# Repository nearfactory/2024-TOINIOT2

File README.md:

# TOINIOT2 2024 Main-Repo

TOINIOT² 2024年度 開発用メインリポジトリ

回路/基板データ・CADデータ・プログラムコード・プレゼンシートなどのデータ共有/保存用

[現時点での設計](https://a360.co/4b5pnYN)

[チーム内Wiki](https://github.com/nearfactory/2024-TOINIOT2/wiki)

## Follow us!

* X (Twitter) | [@toiniot2](https://x.com/toiniot2/)

* Instagram | [toiniot2](https://www.instagram.com/toiniot2/)

* YouTube | [@TOINIOT2](https://www.youtube.com/channel/UCjIjmQF-FIEdHT7s-4lD-6A)

* Team Blog | [TOINIOT² Blog](https://toiniot2-wakayama.github.io/Main/index.html)

## Presentation-Sheet

### 関西ブロック大会 2025.01.14 掲出

### リツモリカップ 2025.02.23 掲出

## Rules
* 📂 Discord上の _#GitHub_ チャンネルを活用してアップロード済みデータについての情報交換をしっかり!

* 🗣 コミュニケーションを頻繁にとる!!!!

* 👣 目標は高く、活動は地道に。

* 🧪 実験を実験を面倒くさがらない、小さな実験の積み重ねでロボットは完成する。

* 📚 率先して技術・知識の習得につとめる。

* 🤜 自らの担当に縛られすぎず、他の担当の手伝いもできるとベスト。

* 👥 自分が困っているときは遠慮なくメンバーにヘルプを求め、メンバーが困っているときは躊躇せずヘルプする!!!!

* 💪 **これが最後のRCJ。やり残しがないようにしよう。**

## Members
* NearFactory [@nearfactory](https://x.com/nearfactory/)

  機体設計・回路/基板設計・プログラム・プレゼンシート　担当

* maguronoosushi0807 [@_Rts87](https://x.com/_Rts87)

  回路/基板設計・プログラム　担当
  
* 010

  広報・ブログ・機体組立て　担当

* tobi

  電池監視員　担当

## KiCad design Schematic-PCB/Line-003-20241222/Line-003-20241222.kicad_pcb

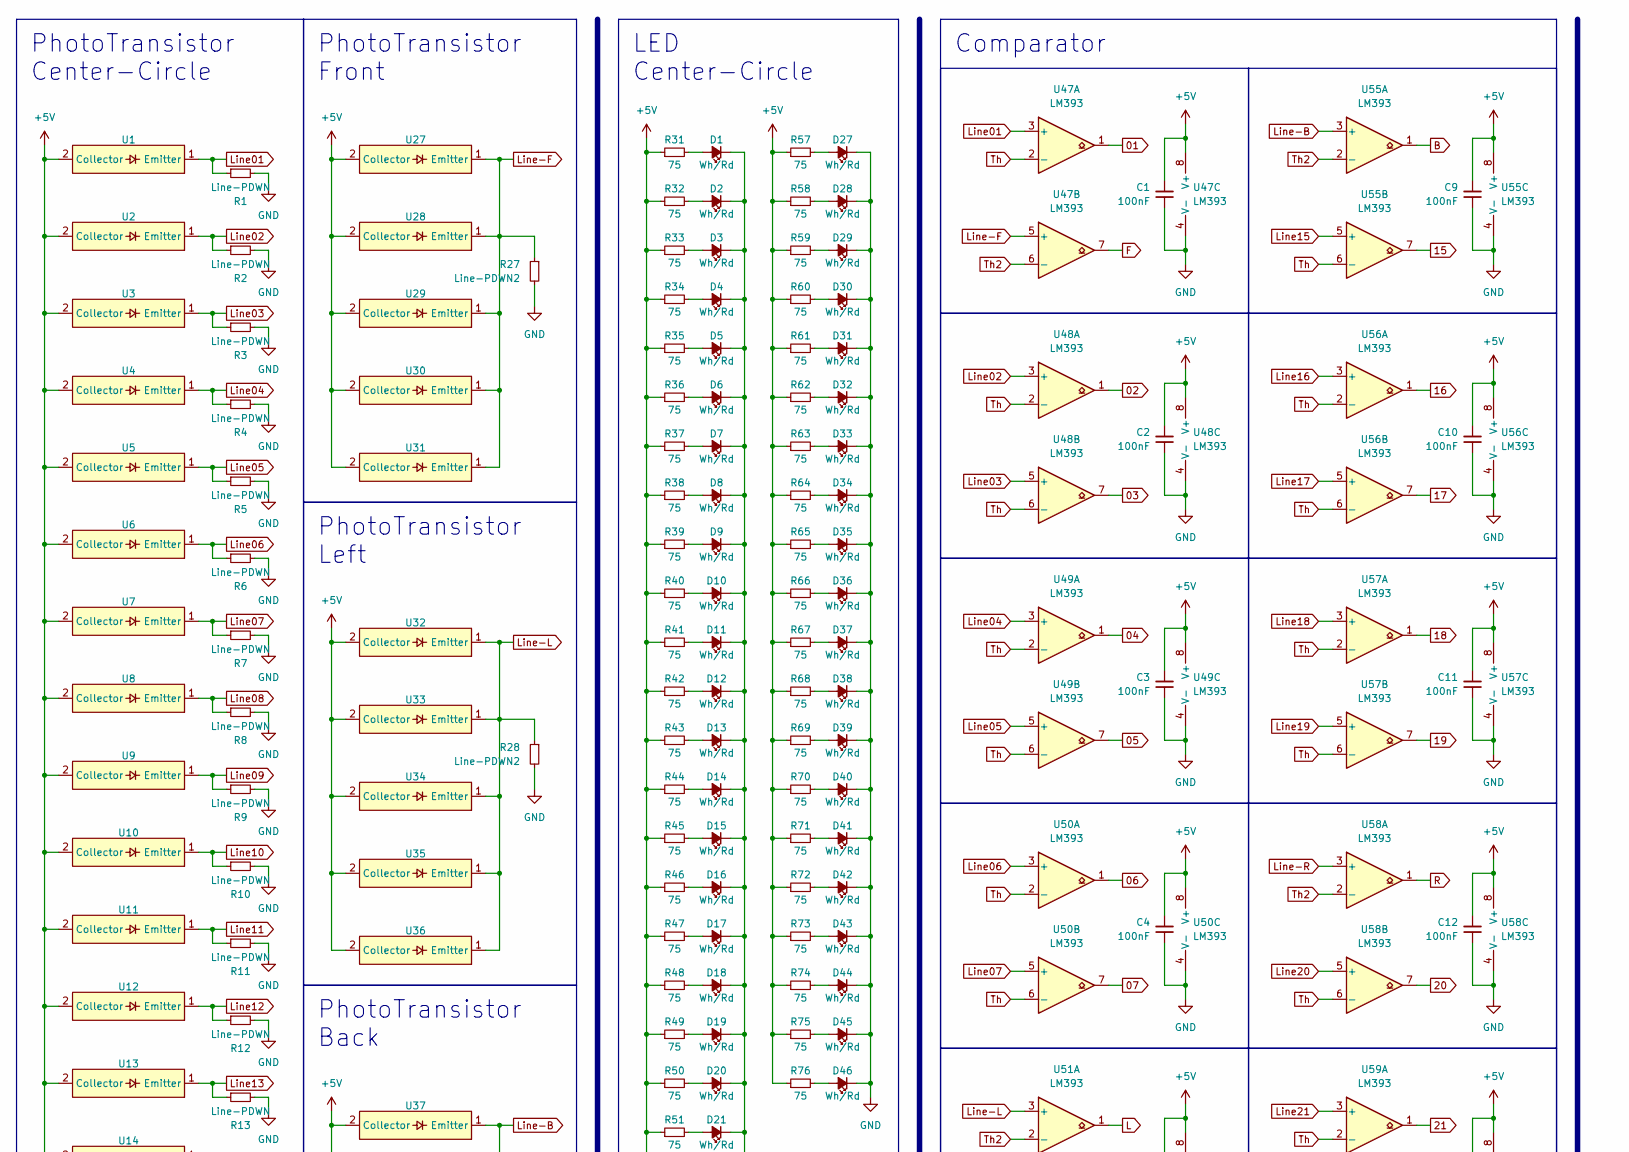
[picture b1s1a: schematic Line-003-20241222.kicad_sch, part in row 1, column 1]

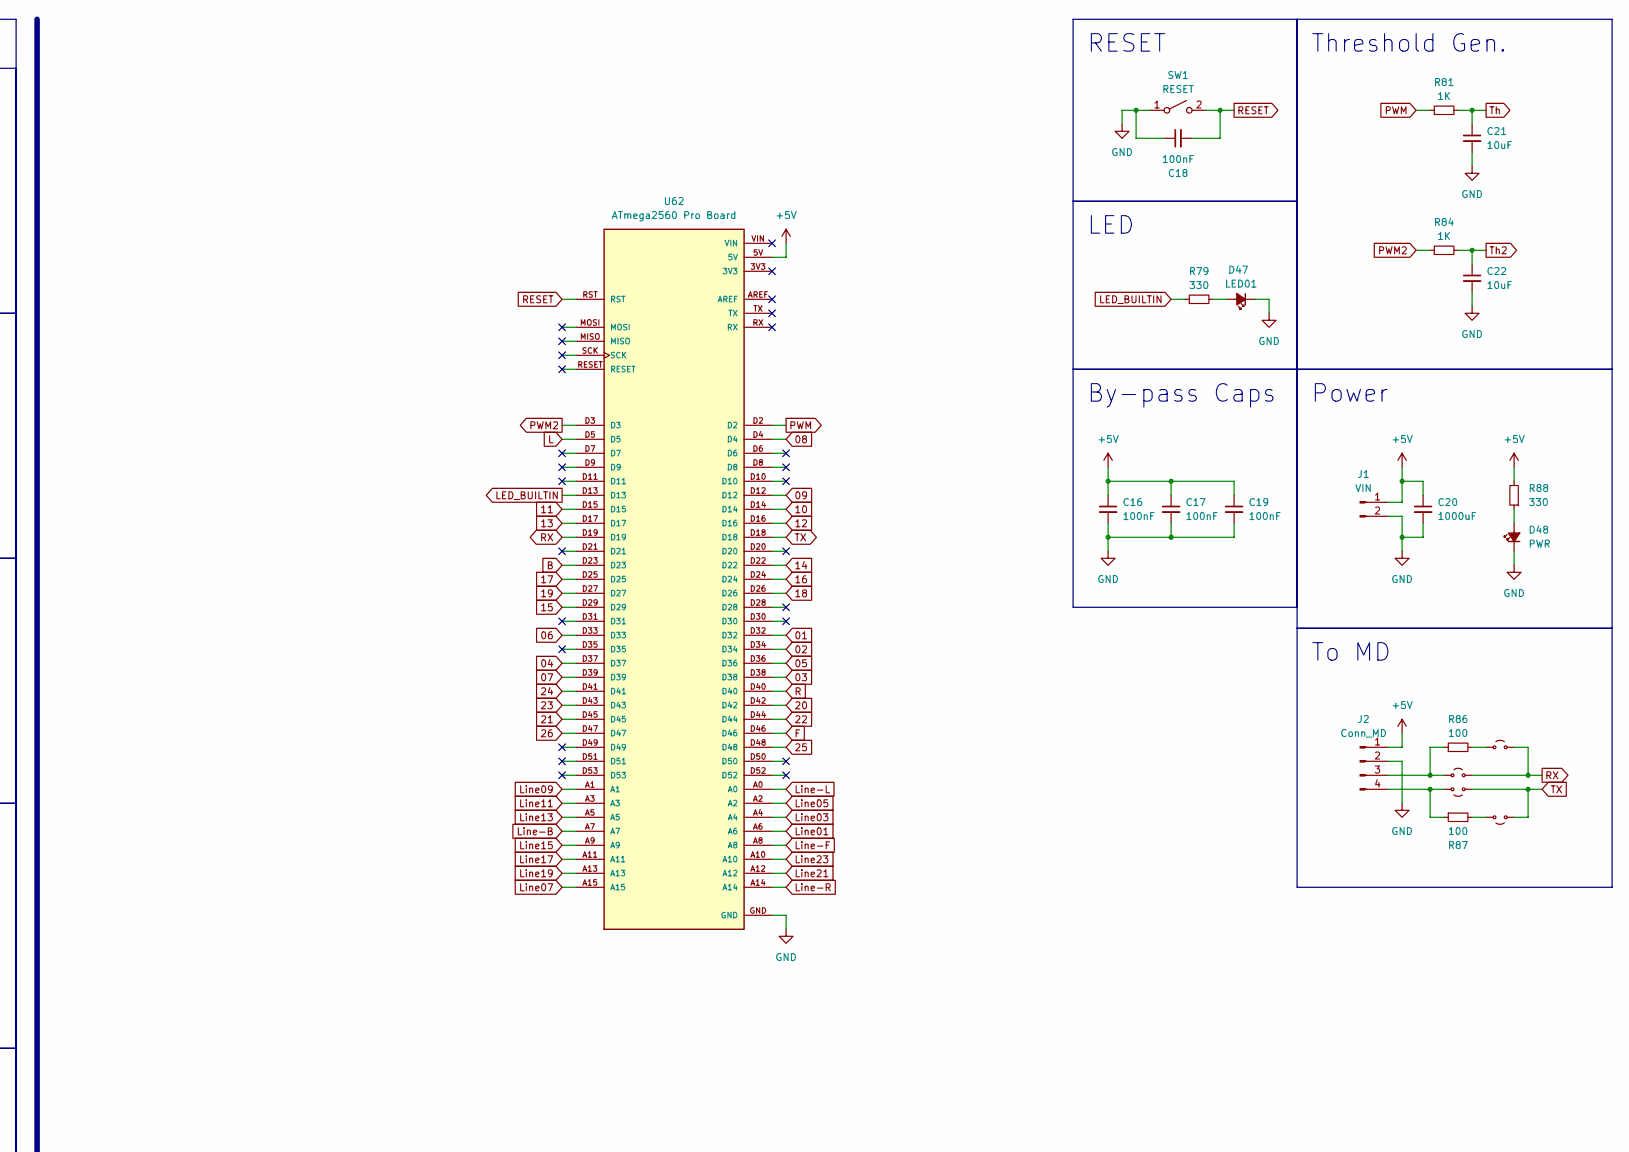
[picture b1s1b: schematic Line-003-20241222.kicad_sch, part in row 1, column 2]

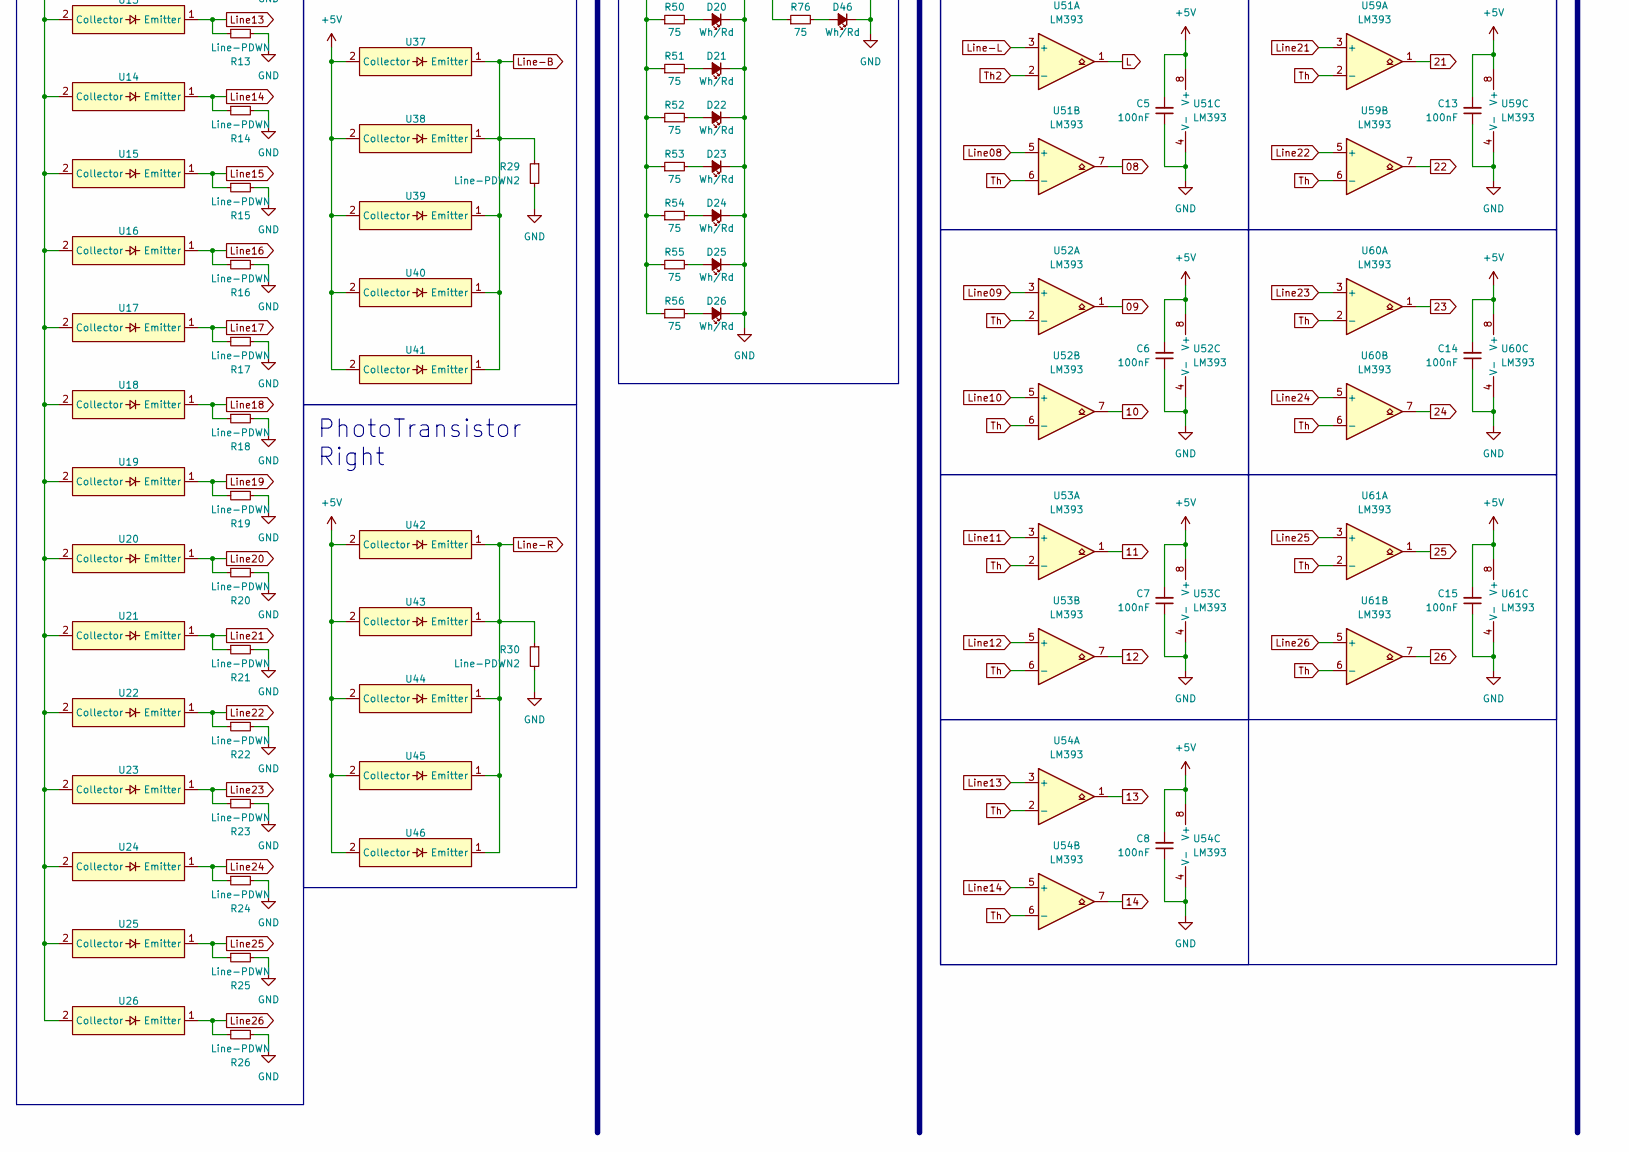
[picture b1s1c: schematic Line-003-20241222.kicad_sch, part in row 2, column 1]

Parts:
C1, C2, C3, C4, C5, C6, C7, C8, C9, C10, C11, C12, C13, C14, C15, C16, C17, C18, C19: 100nF; C_0603_1608Metric
C20: 1000uF; CP_Radial_D10.0mm_P5.00mm
C21, C22: 10uF; C_0805_2012Metric
D1, D2, D3, D4, D5, D6, D7, D8, D9, D10, D11, D12, D13, D14, D15, D16, D17, D18, D19, D20, D21, D22, D23, D24, D25, D26, D27, D28, D29, D30, D31, D32, D33, D34, D35, D36, D37, D38, D39, D40, D41, D42, D43, D44, D45, D46: Wh/Rd; LED-3mm
D47: LED01; LED_0603_1608Metric
D48: PWR; LED_0603_1608Metric
J1: VIN; JST_XH_S2B-XH-A-1_1x02_P2.50mm_Horizontal
J2: Conn_MD; Connector-MD
JP7, JP8, JP9, JP10: Jumper_2_Small_Open; SolderJumper-2_P1.3mm_Open_Pad1.0x1.5mm
R1, R2, R3, R4, R5, R6, R7, R8, R9, R10, R11, R12, R13, R14, R15, R16, R17, R18, R19, R20, R21, R22, R23, R24, R25, R26: Line-PDWN; R_0603_1608Metric
R27, R28, R29, R30: Line-PDWN2; R_0603_1608Metric
R31, R32, R33, R34, R35, R36, R37, R38, R39, R40, R41, R42, R43, R44, R45, R46, R47, R48, R49, R50, R51, R52, R53, R54, R55, R56, R57, R58, R59, R60, R61, R62, R63, R64, R65, R66, R67, R68, R69, R70, R71, R72, R73, R74, R75, R76: 75; R_0603_1608Metric
R79, R88: 330; R_0603_1608Metric
R81, R84: 1K; R_0603_1608Metric
R86, R87: 100; R_0603_1608Metric
SW1: RESET; Tactile1
U1, U2, U3, U4, U5, U6, U7, U8, U9, U10, U11, U12, U13, U14, U15, U16, U17, U18, U19, U20, U21, U22, U23, U24, U25, U26, U27, U28, U29, U30, U31, U32, U33, U34, U35, U36, U37, U38, U39, U40, U41, U42, U43, U44, U45, U46: NJL7502L
U47, U48, U49, U50, U51, U52, U53, U54, U55, U56, U57, U58, U59, U60, U61: LM393; SOP-8_3.9x4.9mm_P1.27mm
U62: ATmega2560 Pro Board; ATmega2560Pro Board; PARTREV 12/May/2017

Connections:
01: U47.1, U62.D32
02: U48.1, U62.D34
03: U48.7, U62.D38
04: U49.1, U62.D37
05: U49.7, U62.D36
06: U50.1, U62.D33
07: U50.7, U62.D39
08: U51.7, U62.D4
09: U52.1, U62.D12
10: U52.7, U62.D14
11: U53.1, U62.D15
12: U53.7, U62.D16
13: U54.1, U62.D17
14: U54.7, U62.D22
15: U55.7, U62.D29
16: U56.1, U62.D24
17: U56.7, U62.D25
18: U57.1, U62.D26
19: U57.7, U62.D27
20: U58.7, U62.D42
21: U59.1, U62.D45
22: U59.7, U62.D44
23: U60.1, U62.D43
24: U60.7, U62.D41
25: U61.1, U62.D48
26: U61.7, U62.D47
+5V: C1.2, C2.2, C3.2, C4.2, C5.2, C6.2, C7.2, C8.2, C9.2, C10.2, C11.2, C12.2, C13.2, C14.2, C15.2, C16.1, C17.1, C19.1, C20.1, J1.1, J2.1, R31.1, R32.1, R33.1, R34.1, R35.1, R36.1, R37.1, R38.1, R39.1, R40.1, R41.1, R42.1, R43.1, R44.1, R45.1, R46.1, R47.1, R48.1, R49.1, R50.1, R51.1, R52.1, R53.1, R54.1, R55.1, R56.1, R57.1, R58.1, R59.1, R60.1, R61.1, R62.1, R63.1, R64.1, R65.1, R66.1, R67.1, R68.1, R69.1, R70.1, R71.1, R72.1, R73.1, R74.1, R75.1, R76.1, R88.2, U1.2 (Collector), U2.2 (Collector), U3.2 (Collector), U4.2 (Collector), U5.2 (Collector), U6.2 (Collector), U7.2 (Collector), U8.2 (Collector), U9.2 (Collector), U10.2 (Collector), U11.2 (Collector), U12.2 (Collector), U13.2 (Collector), U14.2 (Collector), U15.2 (Collector), U16.2 (Collector), U17.2 (Collector), U18.2 (Collector), U19.2 (Collector), U20.2 (Collector), U21.2 (Collector), U22.2 (Collector), U23.2 (Collector), U24.2 (Collector), U25.2 (Collector), U26.2 (Collector), U27.2 (Collector), U28.2 (Collector), U29.2 (Collector), U30.2 (Collector), U31.2 (Collector), U32.2 (Collector), U33.2 (Collector), U34.2 (Collector), U35.2 (Collector), U36.2 (Collector), U37.2 (Collector), U38.2 (Collector), U39.2 (Collector), U40.2 (Collector), U41.2 (Collector), U42.2 (Collector), U43.2 (Collector), U44.2 (Collector), U45.2 (Collector), U46.2 (Collector), U47.8 (V+), U48.8 (V+), U49.8 (V+), U50.8 (V+), U51.8 (V+), U52.8 (V+), U53.8 (V+), U54.8 (V+), U55.8 (V+), U56.8 (V+), U57.8 (V+), U58.8 (V+), U59.8 (V+), U60.8 (V+), U61.8 (V+), U62.5V
B: U55.1, U62.D23
F: U47.7, U62.D46
GND: C1.1, C2.1, C3.1, C4.1, C5.1, C6.1, C7.1, C8.1, C9.1, C10.1, C11.1, C12.1, C13.1, C14.1, C15.1, C16.2, C17.2, C18.1, C19.2, C20.2, C21.2, C22.2, D1.1 (K), D2.1 (K), D3.1 (K), D4.1 (K), D5.1 (K), D6.1 (K), D7.1 (K), D8.1 (K), D9.1 (K), D10.1 (K), D11.1 (K), D12.1 (K), D13.1 (K), D14.1 (K), D15.1 (K), D16.1 (K), D17.1 (K), D18.1 (K), D19.1 (K), D20.1 (K), D21.1 (K), D22.1 (K), D23.1 (K), D24.1 (K), D25.1 (K), D26.1 (K), D27.1 (K), D28.1 (K), D29.1 (K), D30.1 (K), D31.1 (K), D32.1 (K), D33.1 (K), D34.1 (K), D35.1 (K), D36.1 (K), D37.1 (K), D38.1 (K), D39.1 (K), D40.1 (K), D41.1 (K), D42.1 (K), D43.1 (K), D44.1 (K), D45.1 (K), D46.1 (K), D47.1 (K), D48.1 (K), J1.2, J2.2, R1.2, R2.2, R3.2, R4.2, R5.2, R6.2, R7.2, R8.2, R9.2, R10.2, R11.2, R12.2, R13.2, R14.2, R15.2, R16.2, R17.2, R18.2, R19.2, R20.2, R21.2, R22.2, R23.2, R24.2, R25.2, R26.2, R27.2, R28.2, R29.2, R30.2, SW1.1 (A), U47.4 (V-), U48.4 (V-), U49.4 (V-), U50.4 (V-), U51.4 (V-), U52.4 (V-), U53.4 (V-), U54.4 (V-), U55.4 (V-), U56.4 (V-), U57.4 (V-), U58.4 (V-), U59.4 (V-), U60.4 (V-), U61.4 (V-), U62.GND
L: U51.1, U62.D5
LED_BUILTIN: R79.1, U62.D13
Line01: R1.1, U1.1 (Emitter), U47.3 (+), U62.A6
Line02: R2.1, U2.1 (Emitter), U48.3 (+)
Line03: R3.1, U3.1 (Emitter), U48.5 (+), U62.A4
Line04: R4.1, U4.1 (Emitter), U49.3 (+)
Line05: R5.1, U5.1 (Emitter), U49.5 (+), U62.A2
Line06: R6.1, U6.1 (Emitter), U50.3 (+)
Line07: R7.1, U7.1 (Emitter), U50.5 (+), U62.A15
Line08: R8.1, U8.1 (Emitter), U51.5 (+)
Line09: R9.1, U9.1 (Emitter), U52.3 (+), U62.A1
Line10: R10.1, U10.1 (Emitter), U52.5 (+)
Line11: R11.1, U11.1 (Emitter), U53.3 (+), U62.A3
Line12: R12.1, U12.1 (Emitter), U53.5 (+)
Line13: R13.1, U13.1 (Emitter), U54.3 (+), U62.A5
Line14: R14.1, U14.1 (Emitter), U54.5 (+)
Line15: R15.1, U15.1 (Emitter), U55.5 (+), U62.A9
Line16: R16.1, U16.1 (Emitter), U56.3 (+)
Line17: R17.1, U17.1 (Emitter), U56.5 (+), U62.A11
Line18: R18.1, U18.1 (Emitter), U57.3 (+)
Line19: R19.1, U19.1 (Emitter), U57.5 (+), U62.A13
Line20: R20.1, U20.1 (Emitter), U58.5 (+)
Line21: R21.1, U21.1 (Emitter), U59.3 (+), U62.A12
Line22: R22.1, U22.1 (Emitter), U59.5 (+)
Line23: R23.1, U23.1 (Emitter), U60.3 (+), U62.A10
Line24: R24.1, U24.1 (Emitter), U60.5 (+)
Line25: R25.1, U25.1 (Emitter), U61.3 (+)
Line26: R26.1, U26.1 (Emitter), U61.5 (+)
Line-B: R29.1, U37.1 (Emitter), U38.1 (Emitter), U39.1 (Emitter), U40.1 (Emitter), U41.1 (Emitter), U55.3 (+), U62.A7
Line-F: R27.1, U27.1 (Emitter), U28.1 (Emitter), U29.1 (Emitter), U30.1 (Emitter), U31.1 (Emitter), U47.5 (+), U62.A8
Line-L: R28.1, U32.1 (Emitter), U33.1 (Emitter), U34.1 (Emitter), U35.1 (Emitter), U36.1 (Emitter), U51.3 (+), U62.A0
Line-R: R30.1, U42.1 (Emitter), U43.1 (Emitter), U44.1 (Emitter), U45.1 (Emitter), U46.1 (Emitter), U58.3 (+), U62.A14
unnamed: D1.2 (A), R31.2
unnamed: D2.2 (A), R32.2
unnamed: D3.2 (A), R33.2
unnamed: D4.2 (A), R34.2
unnamed: D5.2 (A), R35.2
unnamed: D6.2 (A), R36.2
unnamed: D7.2 (A), R37.2
unnamed: D8.2 (A), R38.2
unnamed: D9.2 (A), R39.2
unnamed: D10.2 (A), R40.2
unnamed: D11.2 (A), R41.2
unnamed: D12.2 (A), R42.2
unnamed: D13.2 (A), R43.2
unnamed: D14.2 (A), R44.2
unnamed: D15.2 (A), R45.2
unnamed: D16.2 (A), R46.2
unnamed: D17.2 (A), R47.2
unnamed: D18.2 (A), R48.2
unnamed: D19.2 (A), R49.2
unnamed: D20.2 (A), R50.2
unnamed: D21.2 (A), R51.2
unnamed: D22.2 (A), R52.2
unnamed: D23.2 (A), R53.2
unnamed: D24.2 (A), R54.2
unnamed: D25.2 (A), R55.2
unnamed: D26.2 (A), R56.2
unnamed: D27.2 (A), R57.2
unnamed: D28.2 (A), R58.2
unnamed: D29.2 (A), R59.2
unnamed: D30.2 (A), R60.2
unnamed: D31.2 (A), R61.2
unnamed: D32.2 (A), R62.2
unnamed: D33.2 (A), R63.2
unnamed: D34.2 (A), R64.2
unnamed: D35.2 (A), R65.2
unnamed: D36.2 (A), R66.2
unnamed: D37.2 (A), R67.2
unnamed: D38.2 (A), R68.2
unnamed: D39.2 (A), R69.2
unnamed: D40.2 (A), R70.2
unnamed: D41.2 (A), R71.2
unnamed: D42.2 (A), R72.2
unnamed: D43.2 (A), R73.2
unnamed: D44.2 (A), R74.2
unnamed: D45.2 (A), R75.2
unnamed: D46.2 (A), R76.2
unnamed: D47.2 (A), R79.2
unnamed: D48.2 (A), R88.1
unnamed: J2.3, JP7.1 (A), R86.1
unnamed: J2.4, JP8.1 (A), R87.1
unnamed: JP9.1 (A), R86.2
unnamed: JP10.1 (A), R87.2
PWM: R81.1, U62.D2
PWM2: R84.1, U62.D3
R: U58.1, U62.D40
RESET: C18.2, SW1.2 (B), U62.RST
RX: JP7.2 (B), JP9.2 (B), U62.D19
TX: JP8.2 (B), JP10.2 (B), U62.D18
Th: C21.1, R81.2, U47.2 (-), U48.2 (-), U48.6 (-), U49.2 (-), U49.6 (-), U50.2 (-), U50.6 (-), U51.6 (-), U52.2 (-), U52.6 (-), U53.2 (-), U53.6 (-), U54.2 (-), U54.6 (-), U55.6 (-), U56.2 (-), U56.6 (-), U57.2 (-), U57.6 (-), U58.6 (-), U59.2 (-), U59.6 (-), U60.2 (-), U60.6 (-), U61.2 (-), U61.6 (-)
Th2: C22.1, R84.2, U47.6 (-), U51.2 (-), U55.2 (-), U58.2 (-)

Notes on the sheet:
By-pass Caps
PhotoTransistor Back
LED Center-Circle
PhotoTransistor Front
PhotoTransistor Center-Circle
Threshold Gen.
RESET
LED
Comparator
Power
PhotoTransistor Right
PhotoTransistor Left
To MD

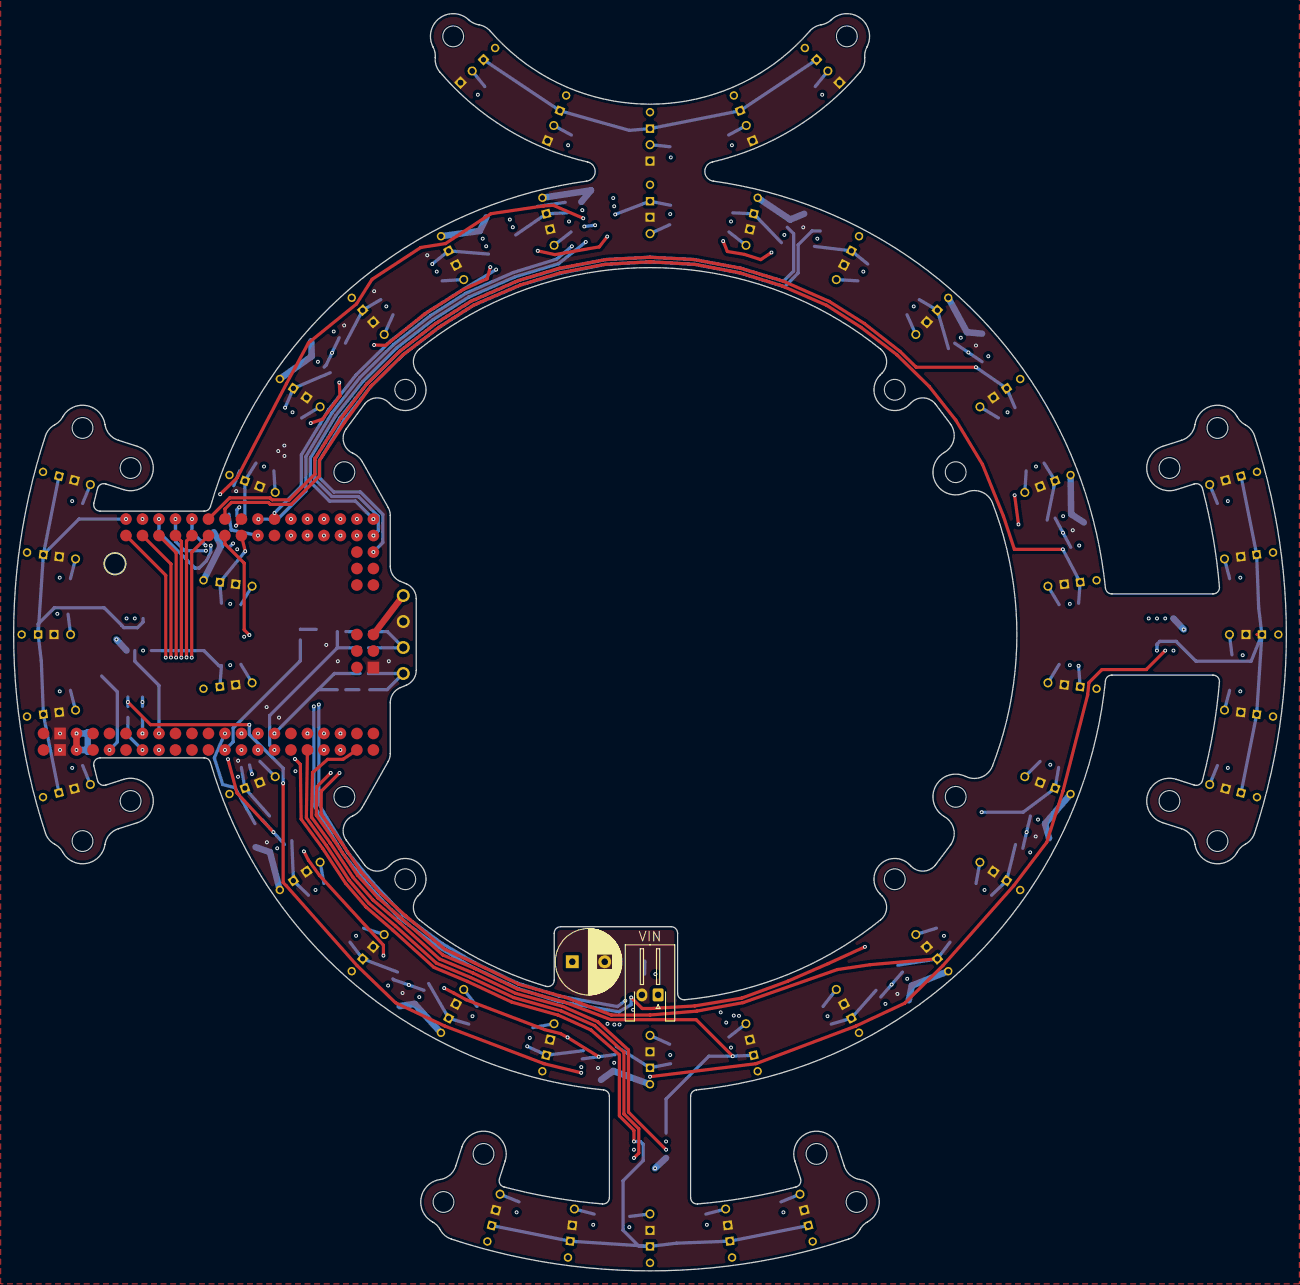
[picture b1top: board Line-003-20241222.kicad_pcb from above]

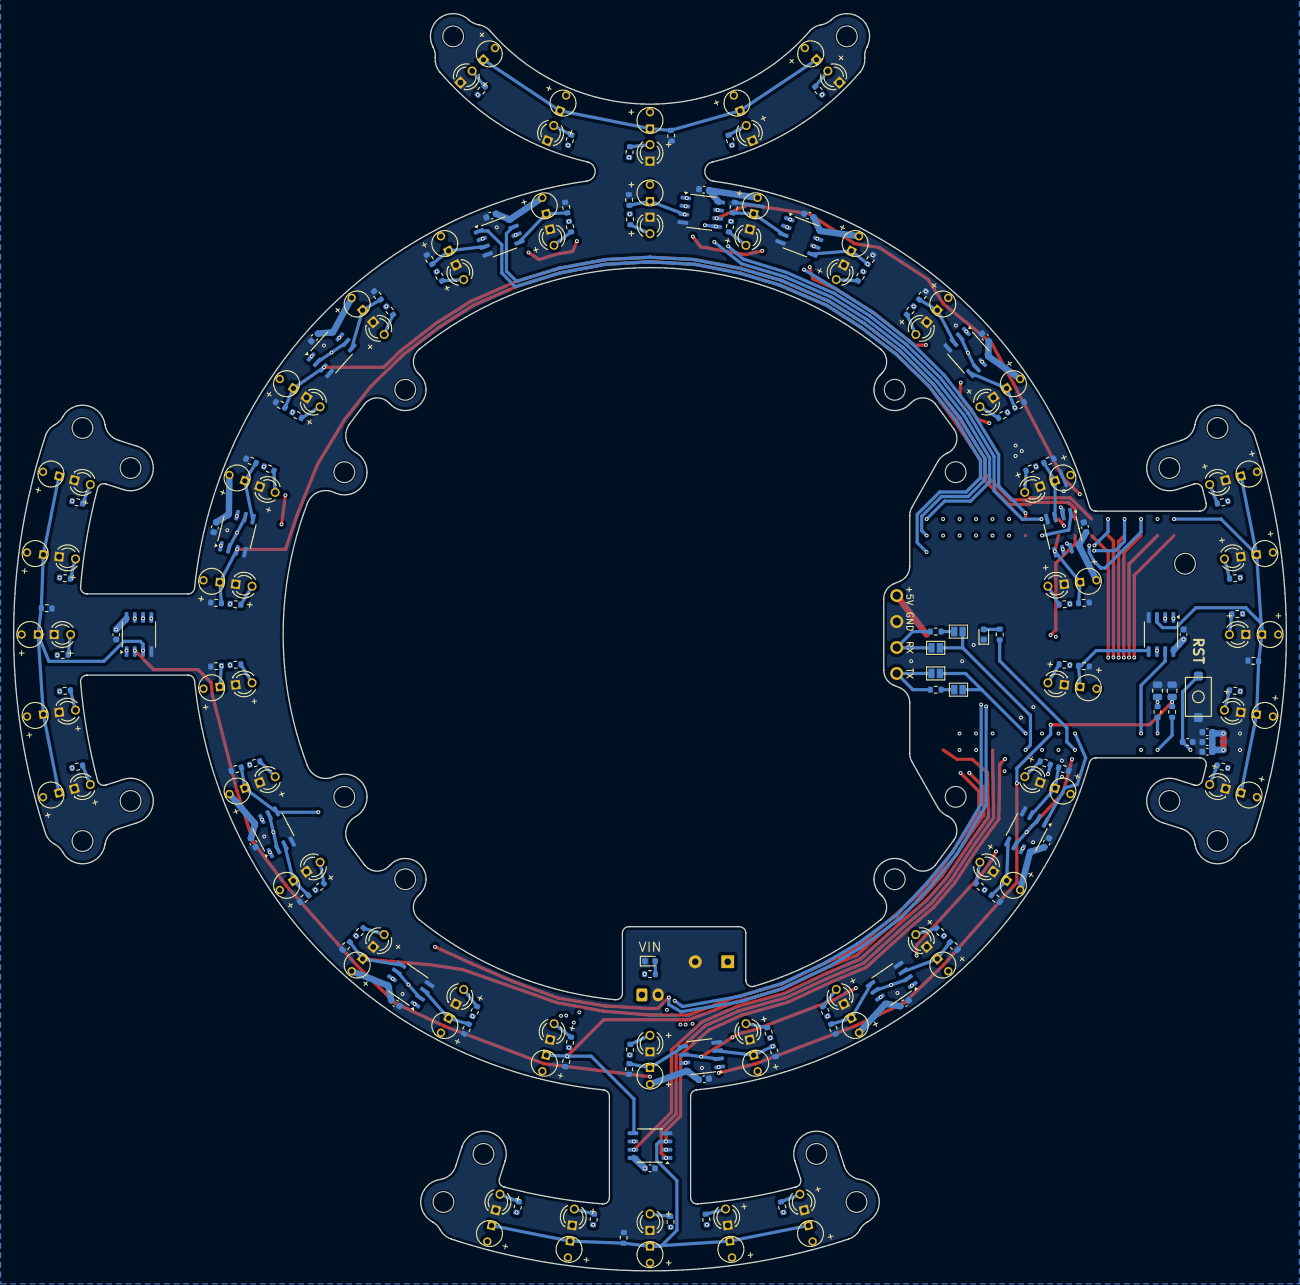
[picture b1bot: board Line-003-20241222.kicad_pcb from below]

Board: 4 copper layers, 196.0 x 193.6 mm, 221 parts (217 on the bottom side), 122 nets.

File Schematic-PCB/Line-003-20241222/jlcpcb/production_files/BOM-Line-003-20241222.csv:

Comment,Designator,Footprint,LCSC,Quantity
100nF,"C1,C10,C11,C12,C13,C14,C15,C16,C17,C18,C19,C2,C3,C4,C5,C6,C7,C8,C9",C_0603_1608Metric,C14663,19
10uF,"C21,C22",C_0805_2012Metric,C15850,2
1K,"R81,R84",R_0603_1608Metric,C21190,2
100,"R86,R87",R_0603_1608Metric,C22775,2
330,"R79,R88",R_0603_1608Metric,C23138,2
Line-PDWN2,"R27,R28,R29,R30",R_0603_1608Metric,C25804,4
RESET,SW1,Tactile1,C2844407,1
Line-PDWN,"R1,R10,R11,R12,R13,R14,R15,R16,R17,R18,R19,R2,R20,R21,R22,R23,R24,R25,R26,R3,R4,R5,R6,R7,R8,R9",R_0603_1608Metric,C4184,26
75,"R31,R32,R33,R34,R35,R36,R37,R38,R39,R40,R41,R42,R43,R44,R45,R46,R47,R48,R49,R50,R51,R52,R53,R54,R55,R56,R57,R58,R59,R60,R61,R62,R63,R64,R65,R66,R67,R68,R69,R70,R71,R72,R73,R74,R75,R76",R_0603_1608Metric,C4275,46
LM393,"U47,U48,U49,U50,U51,U52,U53,U54,U55,U56,U57,U58,U59,U60,U61",SOP-8_3.9x4.9mm_P1.27mm,C7955,15

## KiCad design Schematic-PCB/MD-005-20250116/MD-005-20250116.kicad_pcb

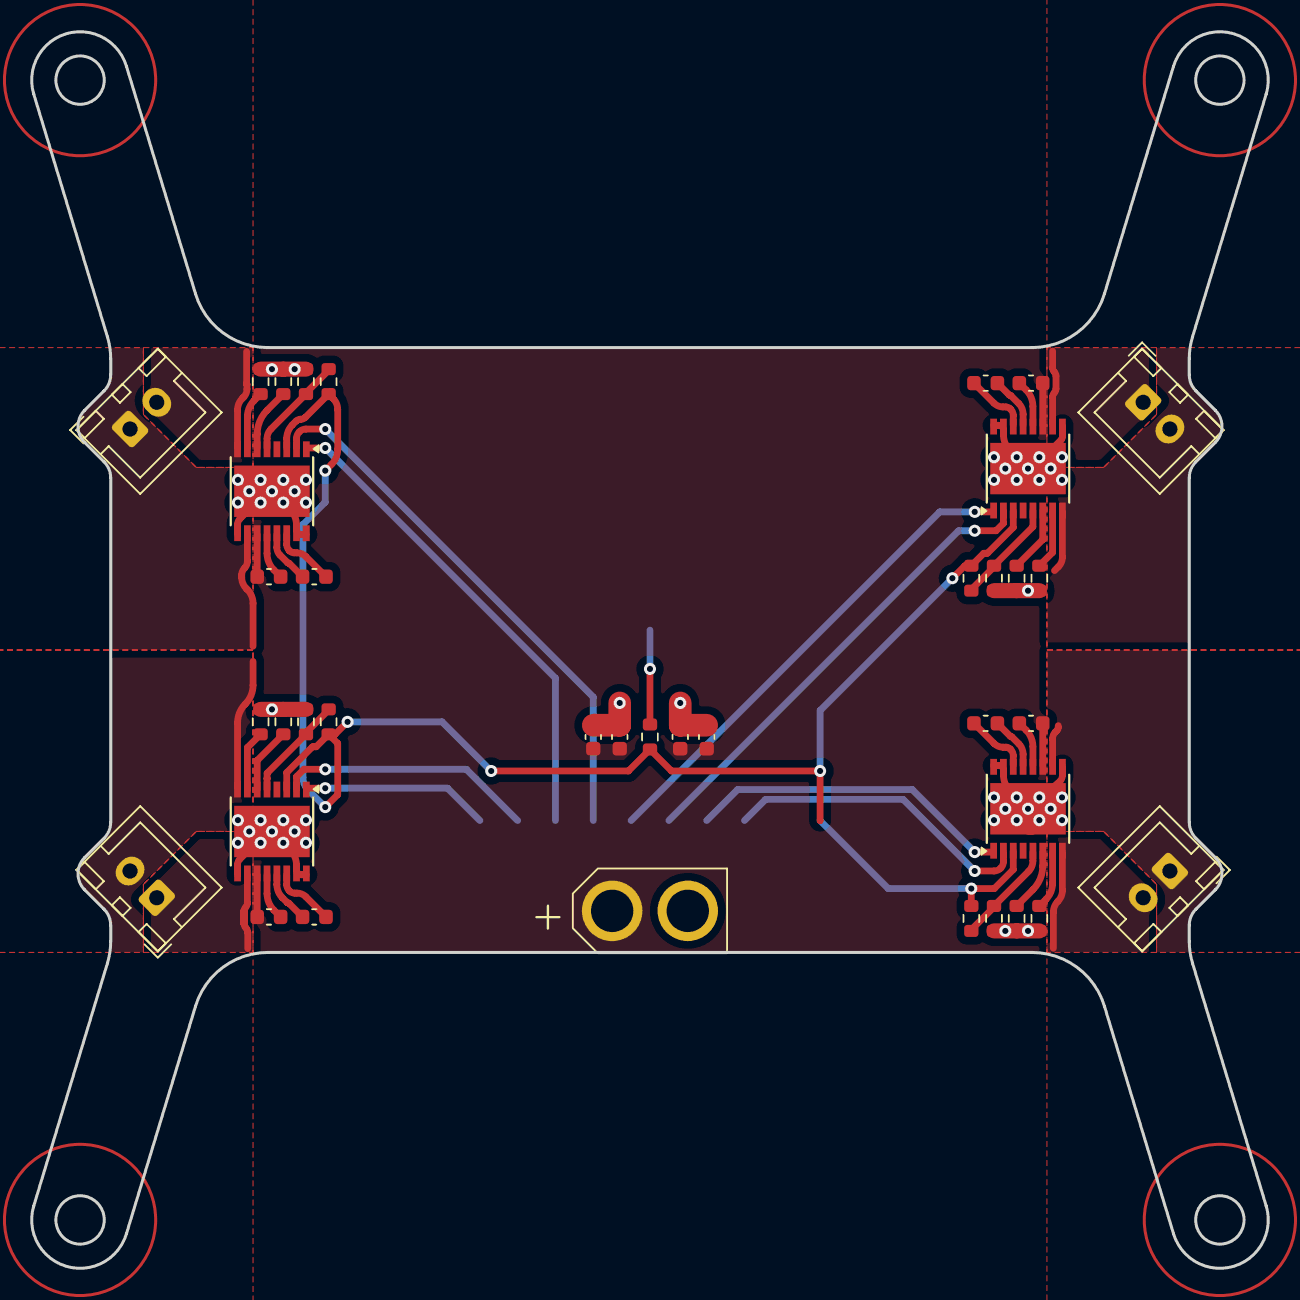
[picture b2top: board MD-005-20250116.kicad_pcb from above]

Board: 2 copper layers, 81.8 x 81.8 mm, 39 parts (1 on the bottom side), 36 nets.

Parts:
C1, C2: 4.7u; C_0603_1608Metric
C3, C4: 0.1u; C_0603_1608Metric
C5, C6, C9, C10: 22n; C_0603_1608Metric
C7, C8, C11, C12: 220n; C_0603_1608Metric
D1: PWR; LED_0805_2012Metric
J1: Conn_PWR; XT30U-M
J3, J4, J5, J6: Conn_01x02_Pin; JST_XH_B2B-XH-A_1x02_P2.50mm_Vertical
R1, R2, R10, R11: 2.49k; R_0603_1608Metric
R3: 330; R_0603_1608Metric
R4, R6, R12, R14: 10k; R_0603_1608Metric
R5, R7, R13, R15: NP; R_0603_1608Metric
R8, R9, R16, R17: 20k; R_0603_1608Metric
U1, U2, U3, U4: HTSSOP-16-1EP_4.4x5mm_P0.65mm_EP3.4x5mm

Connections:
GND: C1.2, C2.2, C3.2, C4.2, D1.1 (K), J1.2, R1.2, R2.2, R5.2, R7.2, R8.2, R9.2, R10.2, R11.2, R13.2, R15.2, R16.2, R17.2, U1.9 (PGND), U1.15 (GND), U1.16 (PMODE), U1.17 (GND), U2.9 (PGND), U2.15 (GND), U2.16 (PMODE), U2.17 (GND), U3.9 (PGND), U3.15 (GND), U3.16 (PMODE), U3.17 (GND), U4.9 (PGND), U4.15 (GND), U4.16 (PMODE), U4.17 (GND)
IMODE-1: R8.1, U1.7 (IMODE)
IMODE-2: R16.1, U2.7 (IMODE)
IMODE-3: R9.1, U3.7 (IMODE)
IMODE-4: R17.1, U4.7 (IMODE)
unnamed: D1.2 (A), R3.2
unnamed: C5.2, U1.13 (CPH)
unnamed: C5.1, U1.14 (CPL)
unnamed: R1.1, U1.6 (IPROPI)
unnamed: C7.1, U1.12 (VCP)
unnamed: C6.2, U2.13 (CPH)
unnamed: C6.1, U2.14 (CPL)
unnamed: R2.1, U2.6 (IPROPI)
unnamed: C8.1, U2.12 (VCP)
unnamed: C9.2, U3.13 (CPH)
unnamed: C9.1, U3.14 (CPL)
unnamed: R10.1, U3.6 (IPROPI)
unnamed: C11.1, U3.12 (VCP)
unnamed: C10.2, U4.13 (CPH)
unnamed: C10.1, U4.14 (CPL)
unnamed: R11.1, U4.6 (IPROPI)
unnamed: C12.1, U4.12 (VCP)
OUT1-1: J3.2, U1.8 (OUT1)
OUT1-2: J4.2, U2.8 (OUT1)
OUT1-3: J5.2, U3.8 (OUT1)
OUT1-4: J6.2, U4.8 (OUT1)
OUT2-1: J3.1, U1.10 (OUT2)
OUT2-2: J4.1, U2.10 (OUT2)
OUT2-3: J5.1, U3.10 (OUT2)
OUT2-4: J6.1, U4.10 (OUT2)
SLEEP-1: R3.1, R4.1, R6.1, R12.1, R14.1, U1.3 (SLEEP), U2.3 (SLEEP), U3.3 (SLEEP), U4.3 (SLEEP)
VCC: C1.1, C2.1, C3.1, C4.1, C7.2, C8.2, C11.2, C12.2, J1.1, U1.11 (VM), U2.11 (VM), U3.11 (VM), U4.11 (VM)
VREF-1: R4.2, R5.1, U1.5 (VREF)
VREF-2: R12.2, R13.1, U2.5 (VREF)
VREF-3: R6.2, R7.1, U3.5 (VREF)
VREF-4: R14.2, R15.1, U4.5 (VREF)

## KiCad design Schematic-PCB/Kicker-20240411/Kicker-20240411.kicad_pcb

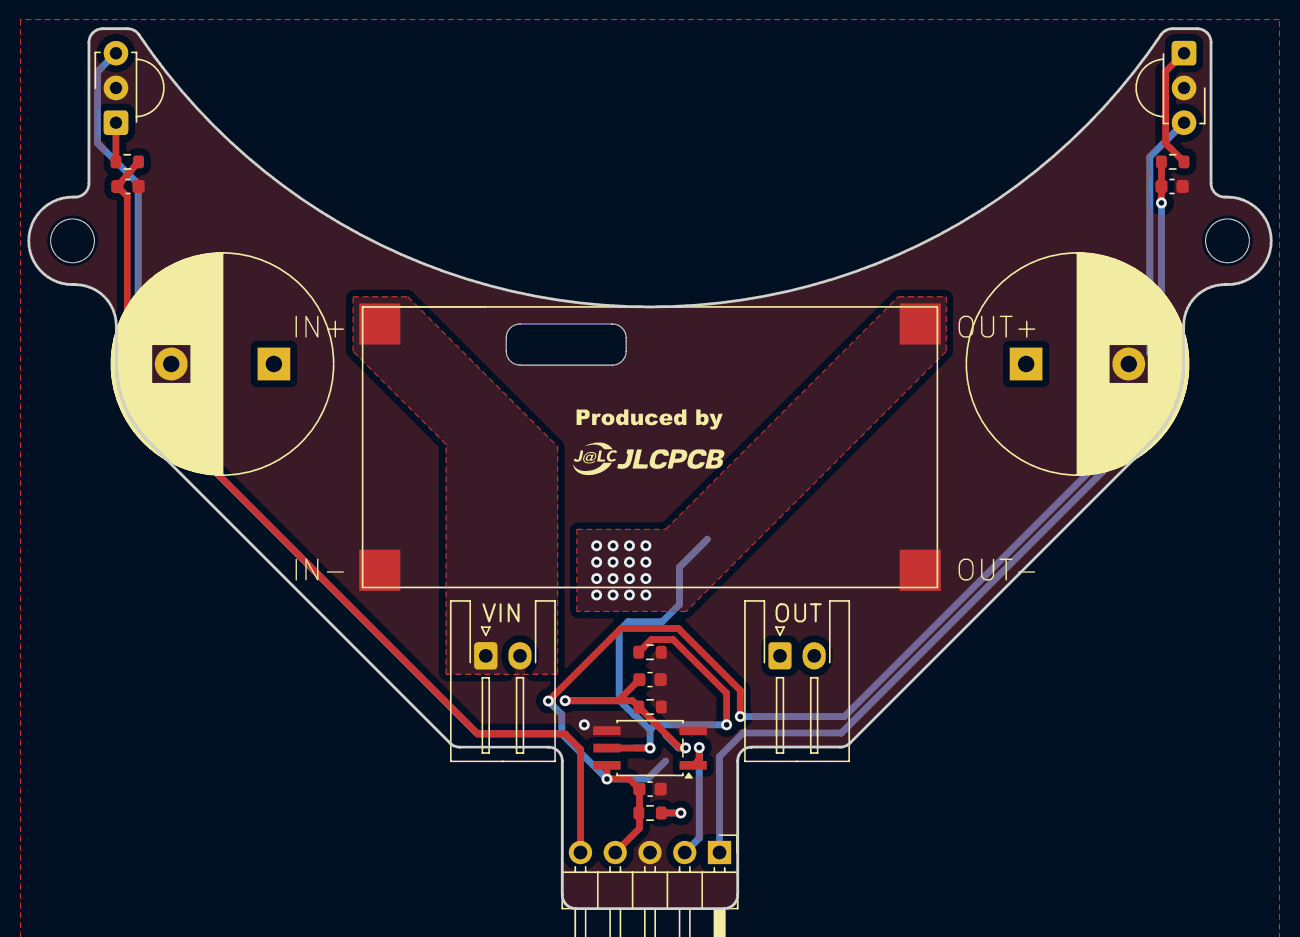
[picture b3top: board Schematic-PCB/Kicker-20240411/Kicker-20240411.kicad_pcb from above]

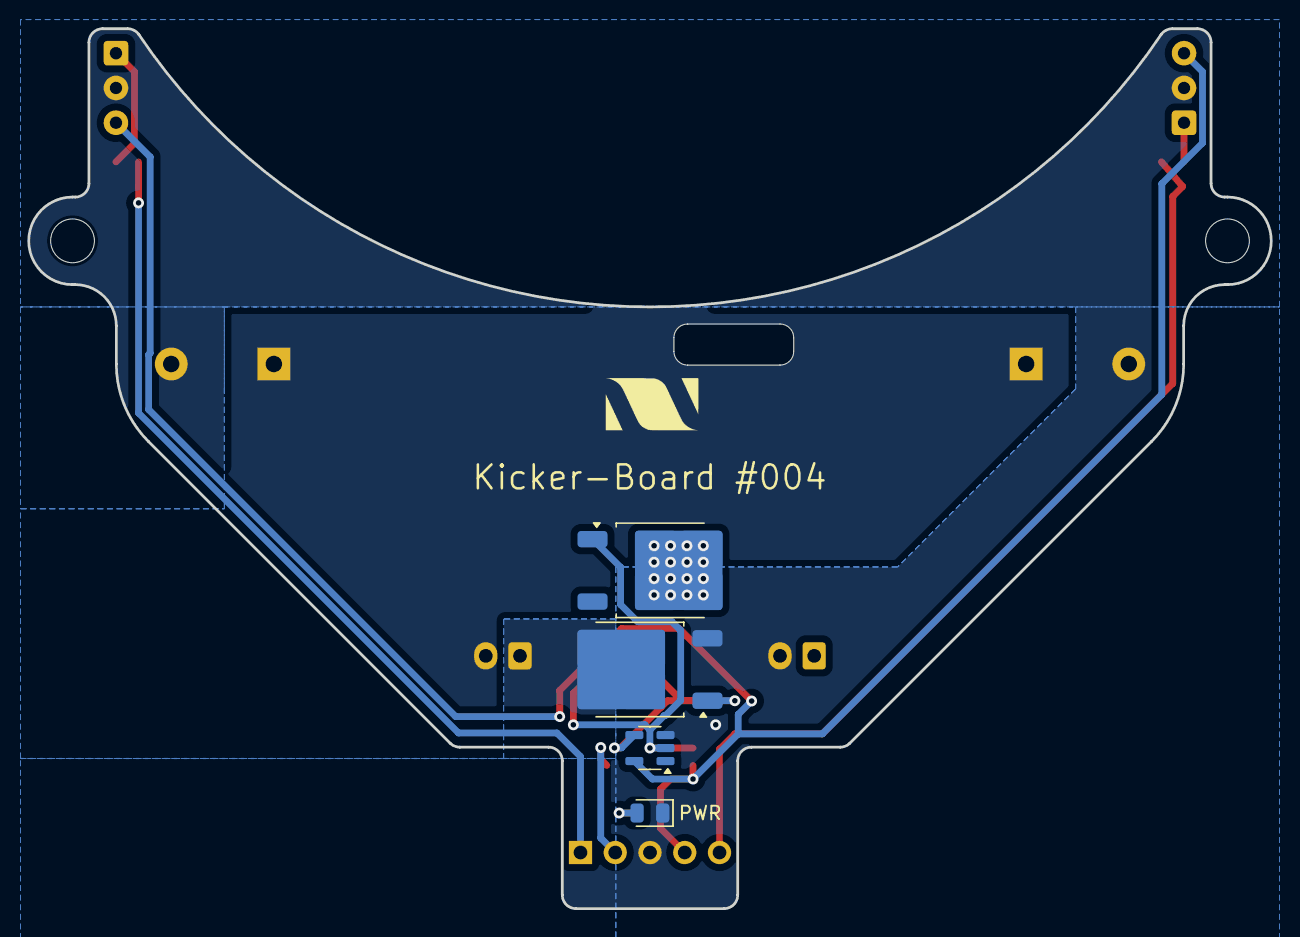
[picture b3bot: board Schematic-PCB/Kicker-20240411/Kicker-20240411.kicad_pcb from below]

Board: 2 copper layers, 90.8 x 64.3 mm, 22 parts (4 on the bottom side), 14 nets.

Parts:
C1, C4: 2200uF; CP_Radial_D16.0mm_P7.50mm
C2, C3: 0.33u; C_0603_1608Metric
C5, C7: 0.1uF; C_0603_1608Metric
D1: PWR; LED_0805_2012Metric
D2: SO-5_4.4x3.6mm_P1.27mm
J1, J3: Conn_01x02_Pin; JST_XH_S2B-XH-A-1_1x02_P2.50mm_Horizontal
J2: Conn_01x05_Pin; PinHeader_1x05_P2.54mm_Horizontal
Q1, Q2: NMOS; TO-252-2
R1, R2: 39K; R_0603_1608Metric
R3: 330; R_0603_1608Metric
R4, R5: 10K; R_0603_1608Metric
U1, U2: TSSP58P38; Vishay_MINICAST-3Pin
U3: XL6009-SMD
U4: SOT-23-5

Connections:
+3.3V: C5.1, D2.6 (VCC), J2.4, R3.1, U1.3 (Vs), U2.3 (Vs), U4.5 (VCC)
+48V: Q1.2 (D), U3.3 (+OUT)
GND: C1.2, C2.2, C3.2, C4.2, C5.2, C7.2, D1.1 (K), D2.3 (Cathode), D2.4 (GND), J1.2, J2.3, Q2.3 (S), R4.2, R5.2, U1.2 (GND), U2.2 (GND), U3.2 (-IN), U3.4 (-OUT), U4.3 (GND)
unnamed: D1.2 (A), R3.2
unnamed: J3.1, Q2.2 (D)
unnamed: C7.1, Q2.1 (G), R5.1, U4.4 (OUT)
unnamed: R1.1, U1.1 (OUT)
unnamed: R2.1, U2.1 (OUT)
Sig: D2.5 (VO), Q1.1 (G), R4.1, U4.2 (IN)
Sig-main: D2.1 (Anode), J2.2
VCC: J1.1, U3.1 (+IN)
VDD: C1.1, C4.1, J3.2
ball01k: C2.1, J2.1, R1.2
ball02k: C3.1, J2.5, R2.2

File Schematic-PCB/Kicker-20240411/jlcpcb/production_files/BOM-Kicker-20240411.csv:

Comment,Designator,Footprint,LCSC
0.33u,"C2,C3",C_0603_1608Metric,C107058
TSSP58P38,"U1,U2",Vishay_MINICAST-3Pin,C144844
0.1uF,"C5,C7",C_0603_1608Metric,C14663
330,R3,R_0603_1608Metric,C23138
39K,"R1,R2",R_0603_1608Metric,C23153
10K,"R4,R5",R_0603_1608Metric,C25804
